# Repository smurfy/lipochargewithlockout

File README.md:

# LiPo/Ion charger with 3V output lockout

Project was born due to an issue with RAK 4631 baseboard solar charger and battery input.
Low battery/charge charge causes brownout and the RAK 4631 needs manual intervention.
In a solar meshtastic node on a mountain thats not convenient.

On meshtastics discourse michimartini came up with a small board to remedy the issue.
Thread: https://meshtastic.discourse.group/t/rak-4631-solar-repeater/7694

## Changelog and short description

### rev1.0

Original board by michimartini supports 450ma charging current.
Not all parts are available at jlcpcb at time of writing but pcb could be built there and parts sourced and assembled manually.

### rev2.0

Adapted for different charge chip, which supports 500ma but also needs resistor for setting it.

* Increased max charge current to 500ma
* switched MCP73811T-420I-OT to MCP73812T-420I-OT for better compatibility
* specified MCP120-xxxxTT as MCP120T-315I/TT

### rev3.0

Switched charge chip again, since i did not like the sound of the charging logic of MCP7381/2 especially related to overcharging/continue charging.
This switch also adds support for a charging led, while not really needed for our use case, its nice to have in testing.

* switched MCP73812T-420I-OT to MCP73831T-2DCI-OT since automatic recharge should work better there
* added charge led

### ref4.0 planning stage

Possible improvements for rev3.0 in the future

* add usb connector for easy charging if solar/jst input is not connected
* adding via's or something for temperature of chargechip, since this is mentioned in datasheet
* switch to CN3065 as charging chip (1000ma, temperature sensing, charged led...)
* add INA219 for solar input measurement (with connector to use sensor port/wires)
* add complete baseboard for RAK4631 (using the cpu port connector)

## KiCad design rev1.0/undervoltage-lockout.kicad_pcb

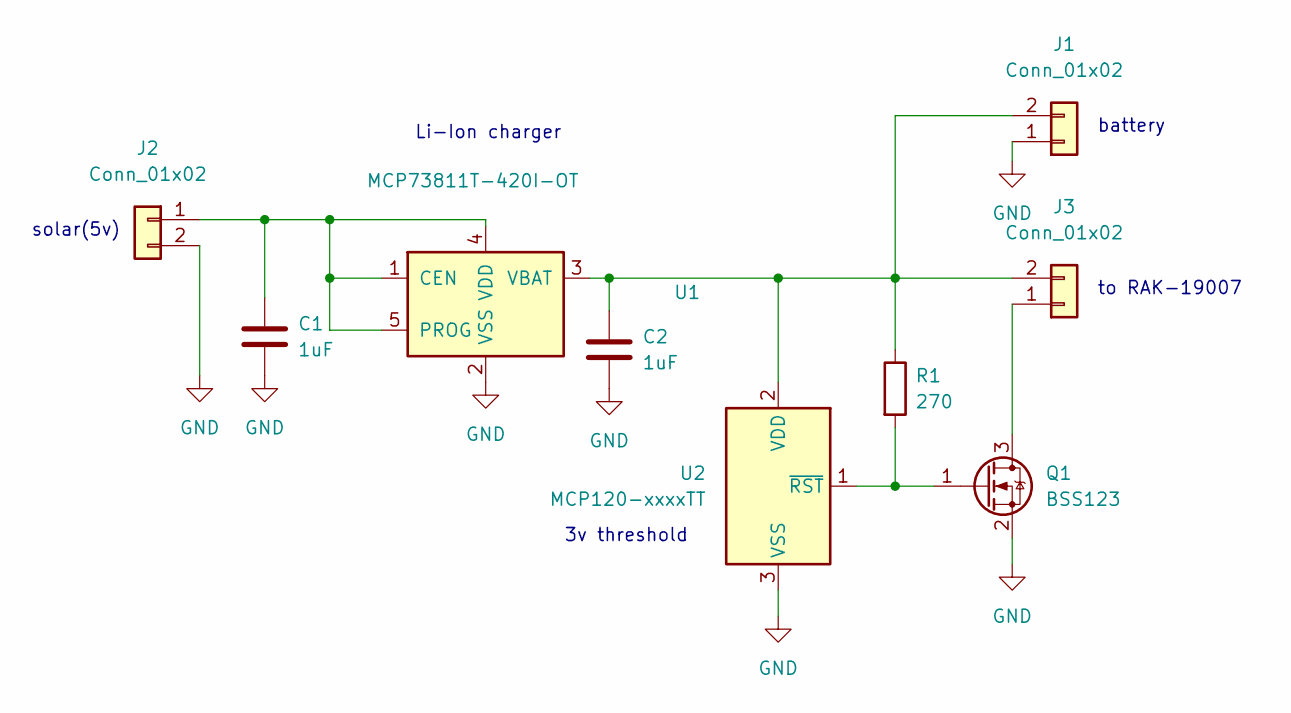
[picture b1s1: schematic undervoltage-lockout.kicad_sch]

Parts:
C1, C2: 1uF; C_0805_2012Metric
J1, J2, J3: Conn_01x02; JST_PH_B2B-PH-K_1x02_P2.00mm_Vertical
Q1: BSS123; SOT-23
R1: 270; R_0603_1608Metric
U1: MCP73811T-420I-OT; SOT-23-5
U2: MCP120-xxxxTT; SOT-23

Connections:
GND: C1.2, C2.2, J1.1, J2.2, Q1.2 (S), U1.2 (VSS), U2.3 (VSS)
unnamed: C1.1, J2.1, U1.1 (CEN), U1.4 (VDD), U1.5 (PROG)
unnamed: C2.1, J1.2, J3.2, R1.1, U1.3 (VBAT), U2.2 (VDD)
unnamed: J3.1, Q1.3 (D)
unnamed: Q1.1 (G), R1.2, U2.1 (~RST)

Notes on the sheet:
Li-Ion charger
to RAK-19007
3v threshold
battery
solar(5v)

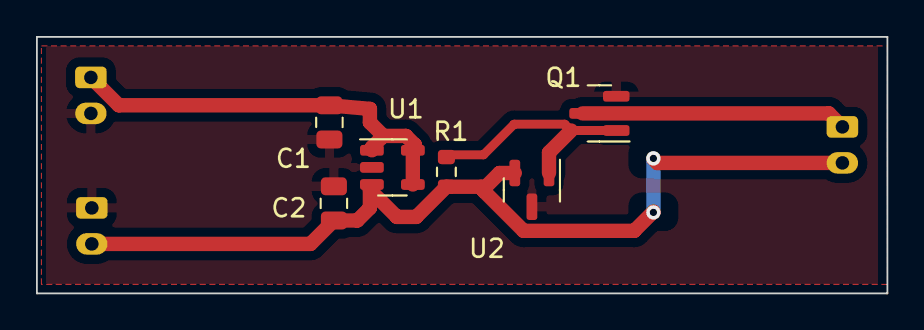
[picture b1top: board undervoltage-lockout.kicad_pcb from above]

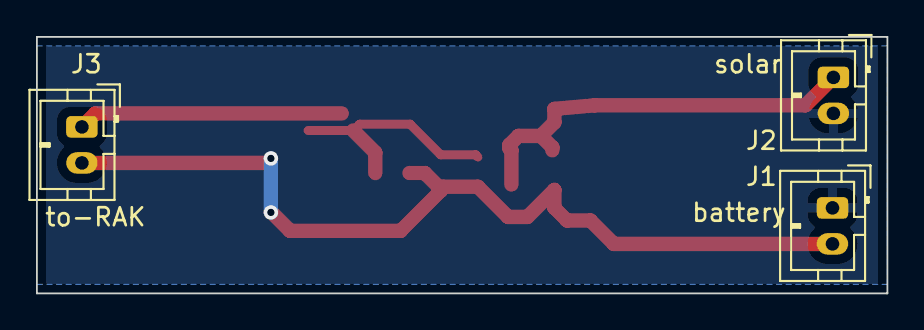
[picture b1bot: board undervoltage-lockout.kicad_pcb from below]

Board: 2 copper layers, 47.2 x 14.2 mm, 9 parts (3 on the bottom side), 5 nets.

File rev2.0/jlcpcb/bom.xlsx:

Comment | Designator | Footprint | JLCPCB Part #（optional）
1uF | C1,C2 | C_0805_2012Metric | C28323
BSS123 | Q1 | SOT-23 | C18198442
MCP120T-315I/TT | U2 | SOT-23 | C461581
270Ω | R1 | R_0603_1608Metric | C22966
MCP73812T-420I-OT | U1 | SOT-23-5 | C144308
2KΩ | R2 | R_0603_1608Metric | C22975

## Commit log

2024-09-17 chore: init repo
2024-09-17 chore: added original design by michimartini
2024-09-17 chore: added rev2.0
2024-09-17 chore: added readme
2024-09-17 chore: added rev3.0
